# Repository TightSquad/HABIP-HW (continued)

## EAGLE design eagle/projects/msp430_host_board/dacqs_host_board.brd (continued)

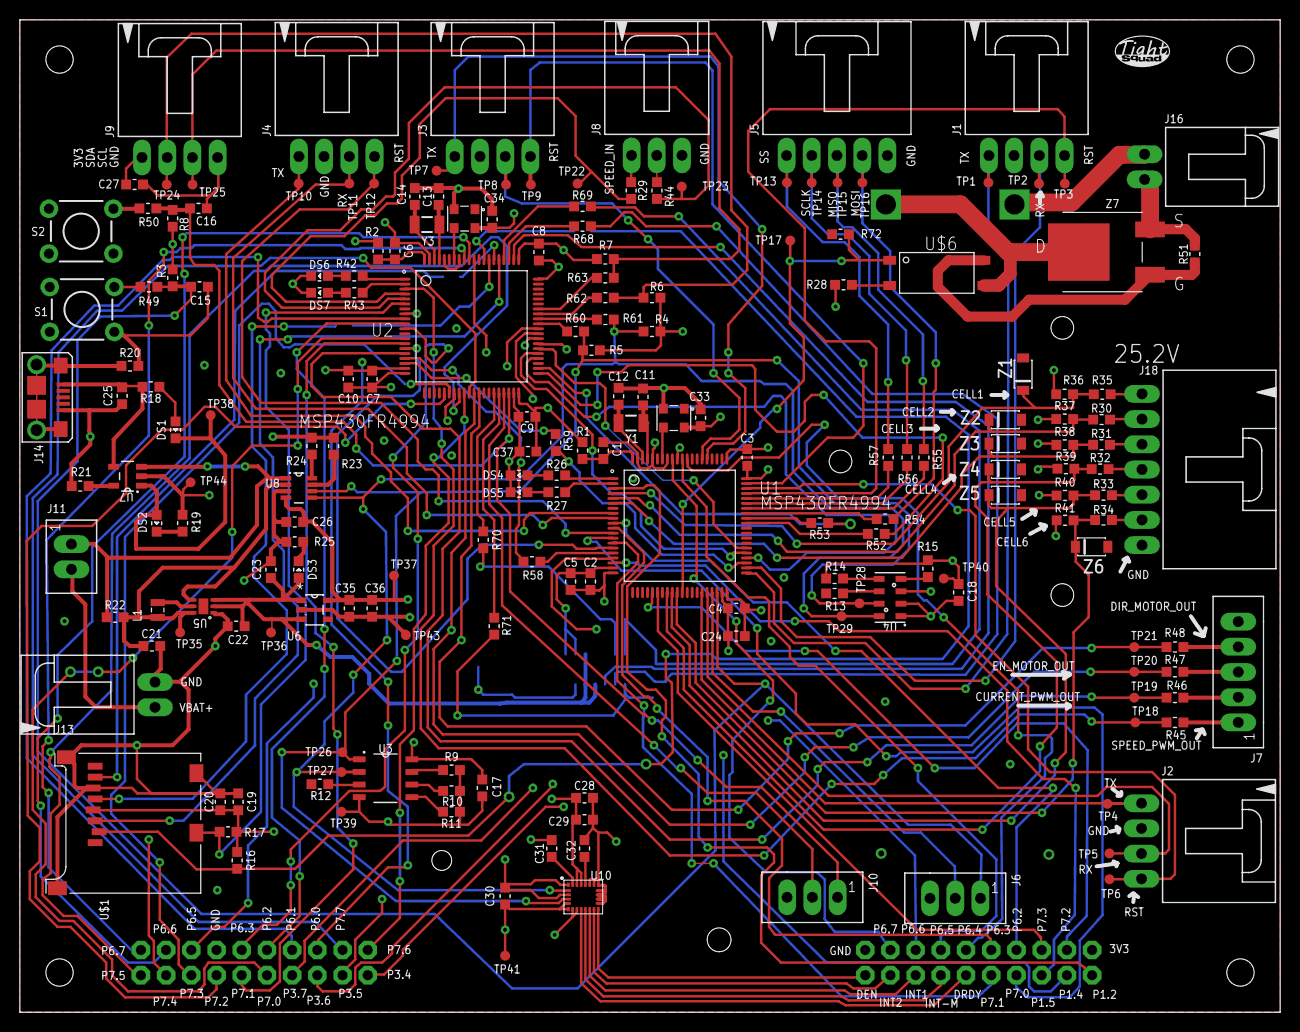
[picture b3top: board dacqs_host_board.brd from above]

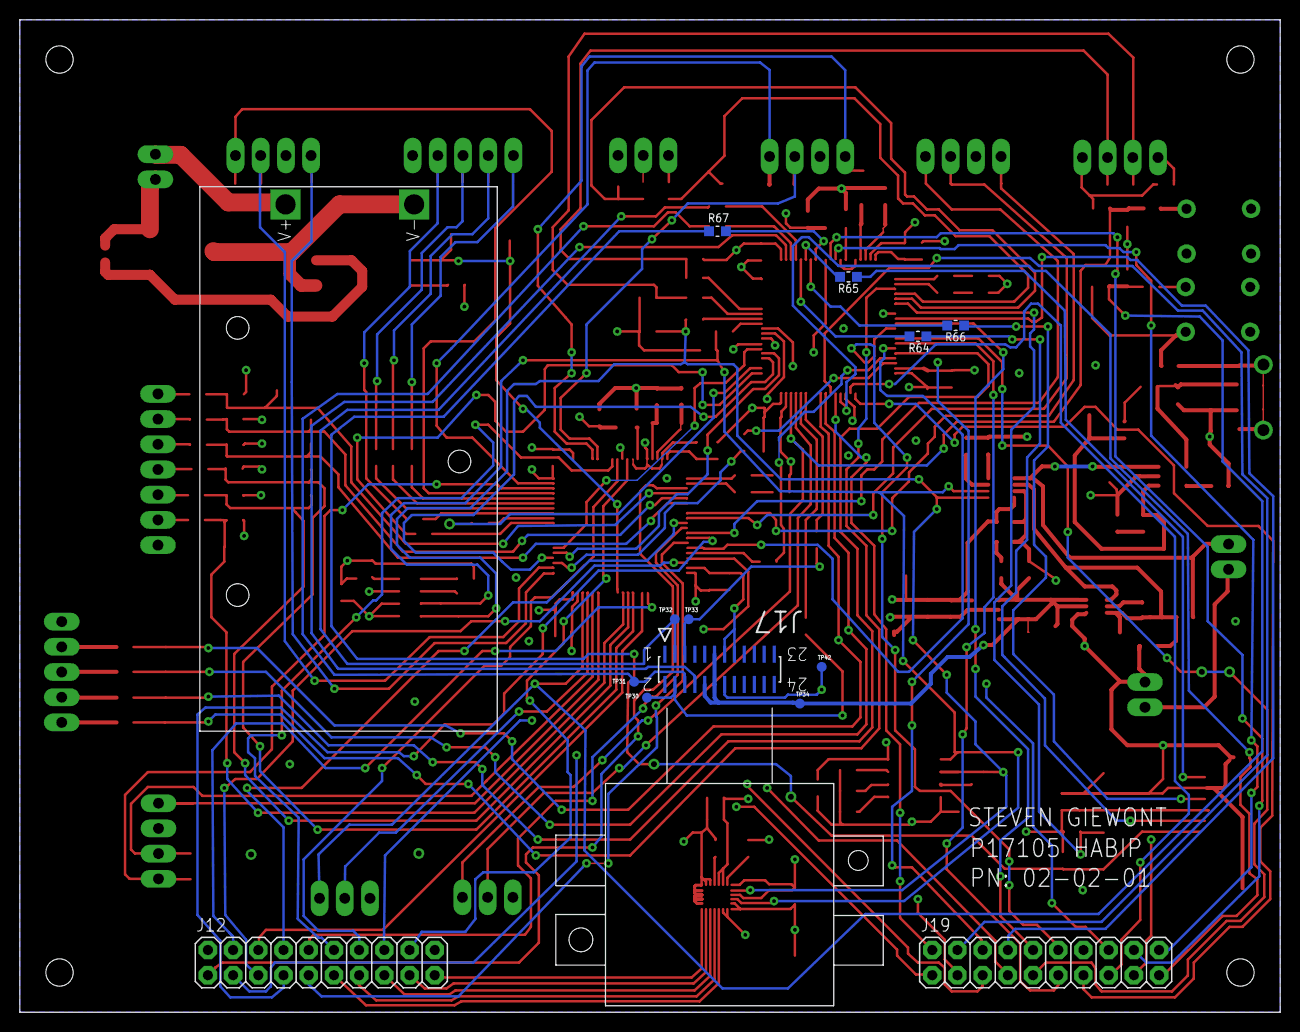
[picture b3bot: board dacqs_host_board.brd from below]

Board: 4 copper layers, 127.0 x 100.0 mm, 272 parts (14 on the bottom side), 172 nets.

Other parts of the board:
U$8: SQUAD_LOGO

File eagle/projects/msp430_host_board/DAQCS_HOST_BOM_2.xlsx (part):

Qty | Value | Device | Package | Parts | Description | FINISH | MANUFACTURER | MANUFACTURER_PN | MOUNT_ANGLE | TOLERANCE | VALUE | VENDOR | VENDOR_PN
18 | 0 | RES_0R0_0603 | R0603 | R1, R2, R9, R10, R11, R12, R13, R14, R15, R20, R23, R24, R29, R44, R45, R46, R4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 | Chip Resistor |  | Panasonic | ERJ-3GEY0R00V |  | JUMPER | 0 | Digi-key | P0.0GCT-ND
1 | 1-Cell 2500mAh Li-Ion Battery | BOM_LINE_ITEM_BLI11 | BLANK | BOM63 |  |  | Adafruit | 328 |  |  | 1-Cell 2500mAh Li-Ion Battery | Adafruit | 328
3 | 10000pF | CAP_10000PF0_0603 | C0603 | C32, C33, C34 | Chip Capacitor |  | AVX Corporation | 06035C103KAT4A |  | ±10% | 10000pF | Digi-key | 478-10055-1-ND
2 | 1000pF | CAP_1000PF0_0603 | C0603 | C15, C16 | Chip Capacitor |  | Murata | GRM188R71H102KA01D |  | 0.1 | 1000pF | Digi-key | 490-1494-1-ND
1 | 100k | RES_100R0_0603 | R0603 | R17 | Chip Resistor |  | Panasonic | ERJ-3EKF1003V |  | 0.01 | 100k | Digi-key | P100KHCT-ND
17 | 100nF | CAP_100NF0_0603 | C0603 | C1, C2, C3, C4, C6, C7, C8, C9, C17, C18, C20, C26, C27, C29, C30, C31, C36 | Chip Capacitor |  | Murata | GRM188R71C104KA01D |  | 0.1 | 100nF | Digi-key | 490-1532-1-ND
1 | 10k | RES_10R0_0603 | R0603 | R37 | Chip Resistor |  | Panasonic | ERJ-3EKF1002V |  | 0.01 | 10k | Digi-key | P10.0KHCT-ND
5 | 10uF | CAP_10UF0_0603 | C0603 | C5, C10, C25, C28, C35 | Chip Capacitor |  | Murata | GRM188R61A106KE69D |  | 0.1 | 10uF | Digi-key | 490-10474-1-ND
1 | 12k | RES_12R0_0603 | R0603 | R34 | Chip Resistor |  | Panasonic | ERJ-3EKF1202V |  | 0.01 | 12k | Digi-key | P12.0KHCT-ND
2 | 15k | RES_15R0_0603 | R0603 | R38, R39 | Chip Resistor |  | Panasonic | ERJ-3EKF1502V |  | 0.01 | 15k | Digi-key | P15.0KHCT-ND
1 | 1k | RES_1R0_0603 | R0603 | R25 | Chip Resistor |  | Panasonic | ERJ-3EKF1001V |  | 0.01 | 1k | Digi-key | P1.00KHCT-ND
4 | 1uF | CAP_1UF0_0603 | C0603 | C19, C23, C24, C37 | Chip Capacitor |  | Murata | GRM033R61A105ME15D |  | 0.2 | 1uF | Digi-key | 490-13226-1-ND
1 | 1uH | IND_1UH0_0805 | WE-PMI_0805 | L1 | Power Multilayer Inductor |  | Murata | LQM21PN1R0MC0D |  | 0.2 | 1uH | Digi-key | 490-4992-1-ND
1 | 2.2uF | CAP_2UF2_0603 | C0603 | C21 | Chip Capacitor |  | Murata | GRM188R61C225KE15D |  | 0.1 | 2.2uF | Digi-key | 490-3296-1-ND
4 | 2.61k | RES_2R61_0603 | R0603 | R4, R5, R6, R7 | Chip Resistor |  | Panasonic | ERJ-3EKF2611V |  | 0.01 | 2.61k | Digi-key | P2.61KHCT-ND
4 | 22pF | CAP_22PF0_0603 | C0603 | C11, C12, C13, C14 | Chip Capacitor |  | Murata | GQM1885C1H220JB01D |  | 0.05 | 22pF | Digi-Key | 490-3575-1-ND
20 | 23.2 | RES_0R23S2_0603 | R0603 | R52, R53, R54, R55, R56, R57, R58, R59, R60, R61, R62, R63, R64, R65, R66, R67,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 | Chip Resistor |  | Panasonic | ERJ-3EKF23R2V |  | 0.01 | 23.2 | Digi-key | P23.2HCT-ND
7 | 2k | RES_2R0_0603 | R0603 | R18, R19, R21, R26, R27, R42, R43 | Chip Resistor |  | Panasonic | ERJ-3EKF2001V |  | 0.01 | 2k | Digi-key | P2.00KHCT-ND
2 | 30k | RES_30R0_0603 | R0603 | R40, R41 | Chip Resistor |  | Panasonic | ERJ-3EKF3002V |  | 0.01 | 30k | Digi-key | P30.0KHCT-ND
2 | 32.768kHz | CRYSTAL3.2X1.5MM | CRYSTAL-SMD-3.2X1.5MM | Y1, Y3 | Various standard crystals. Proven footprints. |  | Epson | FC-135R |  | 20ppm |  | Digi-key | SER4071CT-ND
1 | 4 | RES_4R0_0603 | R0603 | R22 | Chip Resistor |  | Yageo | RL0603FR-070R4L |  | 0.01 | 4 | Digi-key | 311-.4QCT-ND
1 | 4.7uF | CAP_4UF7_0603 | C0603 | C22 | Chip Capacitor |  | Murata | GRM188R61A475KE15D |  | 0.1 | 4.7uF | Digi-key | 490-10477-1-ND
6 | 47k | RES_47R0_0603 | R0603 | R3, R8, R16, R49, R50, R51 | Chip Resistor |  | Panasonic | ERJ-3EKF4702V |  | 0.01 | 47k | Digi-key | P47.0KHCT-ND
4 | 49.9k | RES_49R9_0603 | R0603 | R28, R32, R33, R35 | Chip Resistor |  | Panasonic | ERJ-3EKF4992V |  | 0.01 | 49.9k | Digi-key | P49.9KHCT-ND
1 | 60.4k | RES_60R4_0603 | R0603 | R30 | Chip Resistor |  | Panasonic | ERJ-3EKF6042V |  | 0.01 | 60.4k | Digi-key | P60.4KHCT-ND
1 | 69.8k | RES_68R8_0603 | R0603 | R31 | Chip Resistor |  | Panasonic | ERJ-3EKF6982V |  | 0.01 | 69.8k | Digi-key | P69.8KHCT-ND
1 | 7.15k | RES_7R15_0603 | R0603 | R36 | Chip Resistor |  | Panasonic | ERJ-3EKF7151V |  | 0.01 | 7.15k | Digi-key | P7.15KHCT-ND
1 | 9V | BC9VPC | BC9VPC | BAT1 | 9V board-mount battery cradle |  | MPD | BH9VPC |  |  |  | Digi-key | BH9V-PC-ND
2 | ASEMB-24MHZ-XY-T | ASEMB-24MHZ-XY-T | ASEMB-24MHZ-XY-T-PAC | U$4, U$5 |  |  | Abracon LLC | ASEMB-24.000MHZ-XY-T |  |  |  | Digi-key | 535-11123-1-ND
3 | BLUE | LED_B3V2WURTH_0603 | LED0603 | DS3, DS5, DS7 | Chip LED |  | Wurth | 150060BS75000 |  |  | BLUE | Digi-key | 732-4966-1-ND
1 | CLM-112-02-L-D-IMU-MOUNT_IMU | CLM-112-02-L-D-IMU-MOUNT_IMU | SAMTEC_CLM-112-02-L-D-IMU-MOUNT | J17 | MICRO SOCKET, 1.0MM, SMD, 2X12WAY |  | SAMTEC | CLM-112-02-L-D |  |  |  | Digi-key | SAM1129-12-ND
2 | CONN HEADER 20POS .100 DBL" | M10X2 | 2X10 | J12, J19 |  |  | Samtec Inc. | TSW-110-07-F-D |  |  | CONN HEADER 20POS .100 DBL" | Digi-key | SAM9002-ND
3 | GREEN | LED_G3V2WURTH_0603 | LED0603 | DS2, DS4, DS6 | Chip LED |  | Wurth | 150060GS75000 |  |  | GREEN | Digi-key | 732-4971-1-ND
1 | INA219AIDCNR | INA219AIDCNR | SOT65P110X045-8N | U8 | 26-V, Bidirectional, Zero-Drift, High-Side, I2C Out Current/Power Monitor |  | Texas Instruments | INA219AIDCNR |  |  | INA219AIDCNR | Digi-key | 296-23770-1-ND
1 | LP5907_DBV_5 | LP5907_DBV_5 | DBV5 | U6 |  |  | Texas Instruments | lp5907_dbv_5 |  |  |  | Digi-key | 296-38557-1-ND
1 | LSM9DS1 | LSM9DS1 | LGA24-8X4 | U10 | LSM9DS1 3D accelerometer, gyroscope & magnetometer |  | STMicroelectronics | LSM9DS1TR |  |  |  | Digi-key | 497-14946-1-ND
1 | MCP73831T | MCP73831T-2ATI/OT | SOT23P110X060-5N | U7 | IC, BATT CHARGER, Li-Ion Li-Polymer, 500 mA |  | Microchip | MCP73831T-2ATI/OT |  |  | MCP73831T | Digi-key | MCP73831T-2ATI/OTCT-ND
1 | MICROSD | MICROSD | MICROSD | U$1 | Micro-SD / Transflash card holder with SPI pinout |  | 3M | 2908-05WB-MG |  |  |  | Digi-key | 3M5607CT-ND
6 | MM3Z3V3B | MM3Z3V3B | MM3Z3V3B | Z1, Z2, Z3, Z4, Z5, Z6 |  |  | Farichild/ON Semiconductor | MM3Z3V3B |  |  | MM3Z3V3B | Digi-key | MM3Z3V3BCT-ND
2 | MOL-SL-2-RA | MOLSL_2PIN_SL2RA_RA | MOLSL-2-RA | J13, J16 | Molex SL Series 2-Position Connector | GOLD | Molex | 705530001 | RIGHT |  | MOL-SL-2-RA | Digi-key | WM4900-ND
1 | MOL-SL-2-V | MOLSL_2PIN_SL2V_V | MOLSL-2-V | J11 | Molex SL Series 2-Position Connector | GOLD | Molex | 705430001 | VERTICAL |  | MOL-SL-2-V | Digi-key | WM4800-ND
1 | MOL-SL-3-RA | MOLSL_3PIN_SL3RA_RA | MOLSL-3-RA | J8 | Molex SL Series 3-Position Connector | GOLD | Molex | 705530002 | RIGHT |  | MOL-SL-3-RA | Digi-key | WM4901-ND
2 | MOL-SL-3-V | MOLSL_3PIN_SL3V_V | MOLSL-3-V | J6, J10 | Molex SL Series 3-Position Connector | GOLD | Molex | 705430002 | VERTICAL |  | MOL-SL-3-V | Digi-key | WM4801-ND
5 | MOL-SL-4-RA | MOLSL_4PIN_SL4RA_RA | MOLSL-4-RA | J1, J2, J3, J4, J9 | Molex SL Series 4-Position Connector | GOLD | Molex | 705530003 | RIGHT |  | MOL-SL-4-RA | Digi-key | WM4902-ND
1 | MOL-SL-5-RA | MOLSL_5PIN_SL4RA_RA | MOLSL-5-RA | J5 | Molex SL Series 5-Position Connector | GOLD | Molex | 705530004 | RIGHT |  | MOL-SL-5-RA | Digi-key | WM4903-ND
1 | MOL-SL-5-V | MOLSL_5PIN_SL4V_V | MOLSL-5-V | J7 | Molex SL Series 5-Position Connector | GOLD | Molex | 705430004 | VERTICAL |  | MOL-SL-5-V | Digi-key | WM4803-ND
1 | MOLSL-7-RA | MOLSL_7PIN_RA | MOLSL-7-RA | J18 | Molex SL Series 6-Position Connector | Gold | Molex | 70553-0111 | Right |  | MOLSL-7-RA | Digi-key | WM4158-ND
1 | MS560702BA03-50 | MS5607-02BA03_8SMD | SMD125P110X060-8N | U4 | Barometric Pressure Sensor, with stainless steel cap |  | TE Connectivity | MS560702BA03-50 |  |  | MS560702BA03-50 | Digi-key | 223-1198-1-ND
2 | MSP430FR4994 | MSP430FR5994IPNR | PN0080A_N | U1, U2 |  |  | Texas Instruments | MSP430FR5994IPNR |  |  | MSP430FR4994
1 | NTD2955T4G | NTD2955T4G | NTD2955T4G | U$7 |  |  | ON Semiconductor | NTD2955T4G |  |  |  | Digi-key | NTD2955T4GOSCT-ND
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
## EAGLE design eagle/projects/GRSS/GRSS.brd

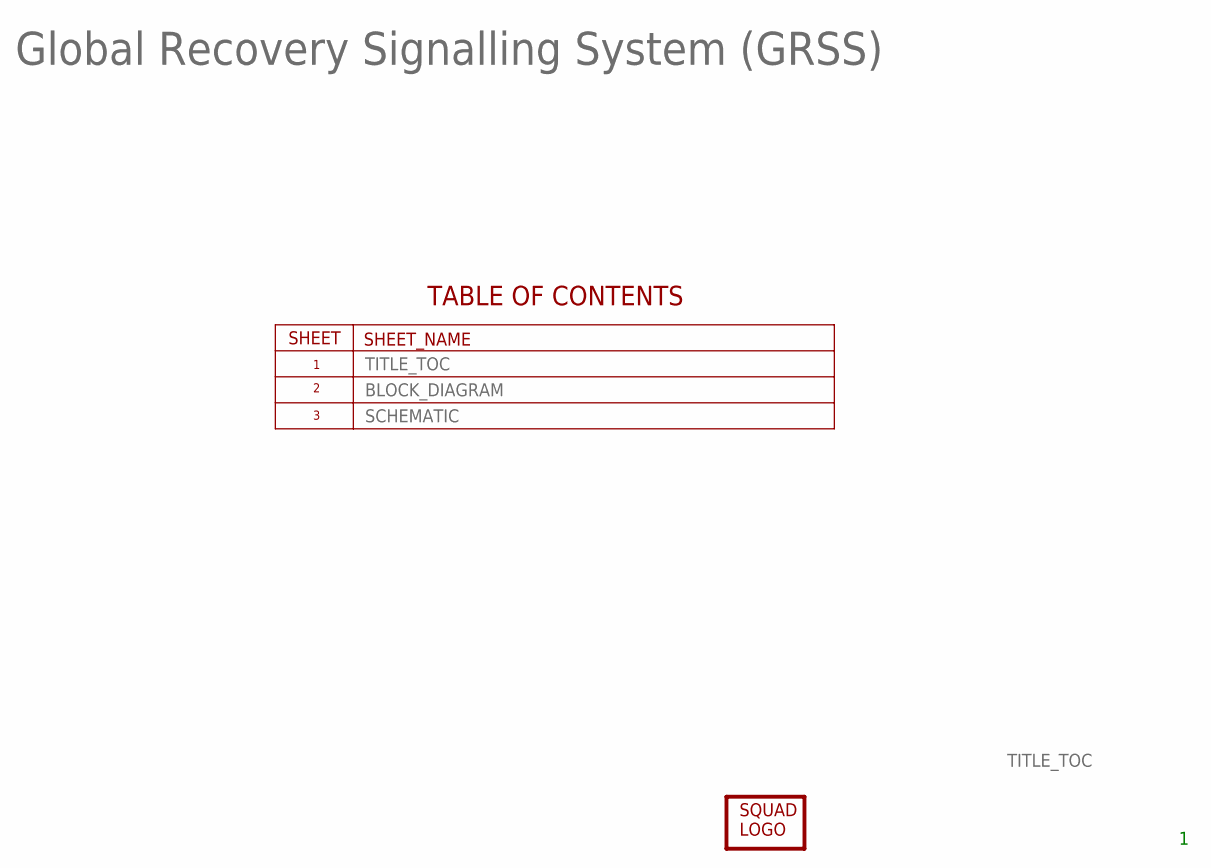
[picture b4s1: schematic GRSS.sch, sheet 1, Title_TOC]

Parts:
LOGO1: LOGO; SQUAD_LOGO

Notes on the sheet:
TITLE_TOC
BLOCK_DIAGRAM
SCHEMATIC
Global Recovery Signalling System (GRSS)

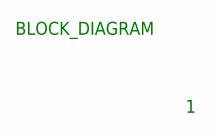
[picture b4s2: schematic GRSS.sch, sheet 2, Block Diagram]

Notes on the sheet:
BLOCK_DIAGRAM

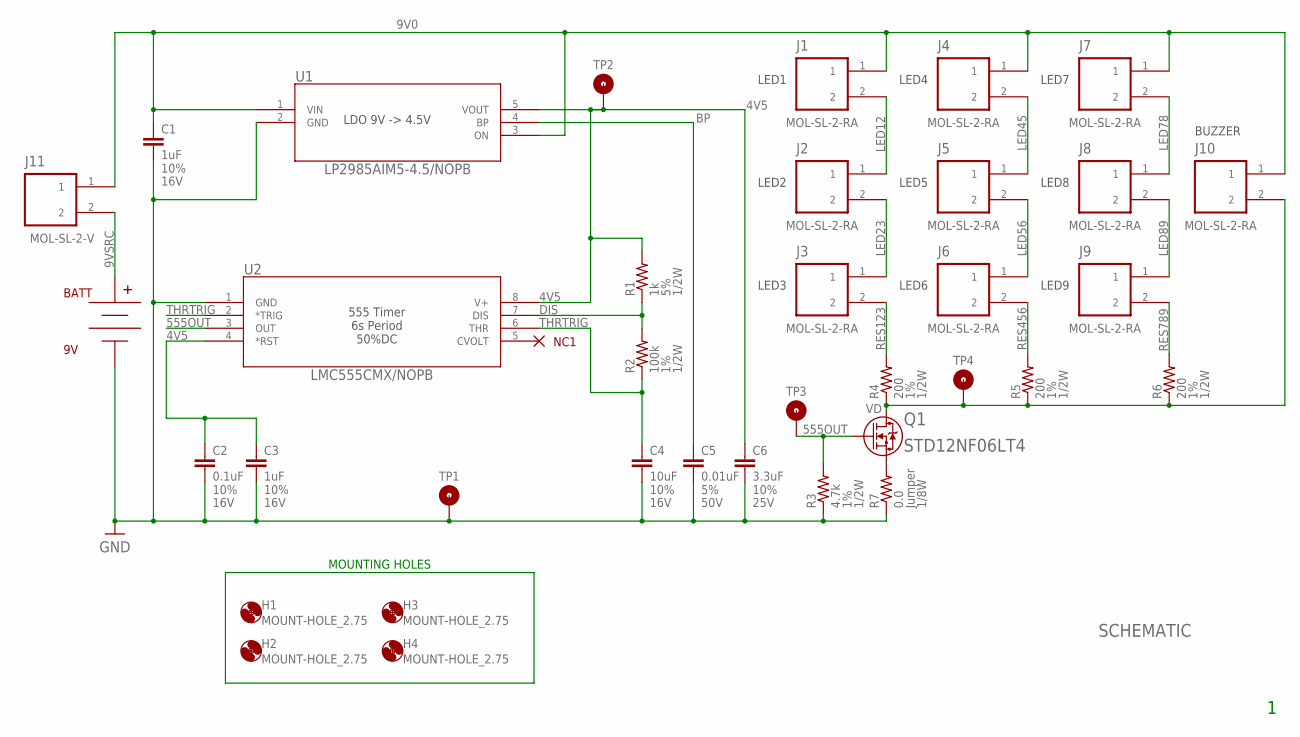
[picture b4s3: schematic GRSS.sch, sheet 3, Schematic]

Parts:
BATT: 9V; BC9VPC
C1, C3: 1uF; C0805
C2: 0.1uF; C0805
C4: 10uF; C0805
C5: 0.01uF; C0805
C6: 3.3uF; C0805
H1, H2, H3, H4: MOUNT-HOLE_2.75; 2,75_HOLE_RASPI
J1, J2, J3, J4, J5, J6, J7, J8, J9, J10: MOL-SL-2-RA; MOLSL-2-RA
J11: MOL-SL-2-V; MOLSL-2-V
Q1: STD12NF06LT4; DPAK
R1: 1k; R0805
R2: 100k; R0805
R3: 4.7k; R0805
R4, R5, R6: 200; R0805
R7: 0.0; R0805
TP1: GND; TP10R
TP2: 4V5; TP10R
TP3: 555OUT; TP10R
TP4: VD; TP10R
U1: LP2985AIM5-4.5/NOPB; MF05A
U2: LMC555CMX/NOPB; M08A

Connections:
4V5: C2.1, C3.1, C6.1, R1.2, TP2.TP, U1.5 (VOUT), U2.4 (*RST), U2.8 (V+)
9V0: C1.1, J1.1, J4.1, J7.1, J10.1, J11.1, U1.1 (VIN), U1.3 (ON)
9VSRC: BATT.V+, J11.2
555OUT: Q1.1, R3.2, TP3.TP, U2.3 (OUT)
BP: C5.1, U1.4 (BP)
DIS: R1.1, R2.2, U2.7 (DIS)
GND: BATT.V-, C1.2, C2.2, C3.2, C4.2, C5.2, C6.2, R3.1, R7.1, TP1.TP, U1.2 (GND), U2.1 (GND)
LED12: J1.2, J2.1
LED23: J2.2, J3.1
LED45: J4.2, J5.1
LED56: J5.2, J6.1
LED78: J7.2, J8.1
LED89: J8.2, J9.1
NC: U2.5 (CVOLT)
RES123: J3.2, R4.2
RES456: J6.2, R5.2
RES789: J9.2, R6.2
THRTRIG: C4.1, R2.1, U2.2 (*TRIG), U2.6 (THR)
VD: J10.2, Q1.3 (2), R4.1, R5.1, R6.1, TP4.TP
ZEROOHM: Q1.2 (3), R7.2

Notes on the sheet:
LED1
LED2
LED3
LED4
LED5
LED6
LED7
LED8
LED9
BUZZER
555 Timer 6s Period 50%DC
LDO 9V -> 4.5V
SCHEMATIC
MOUNTING HOLES

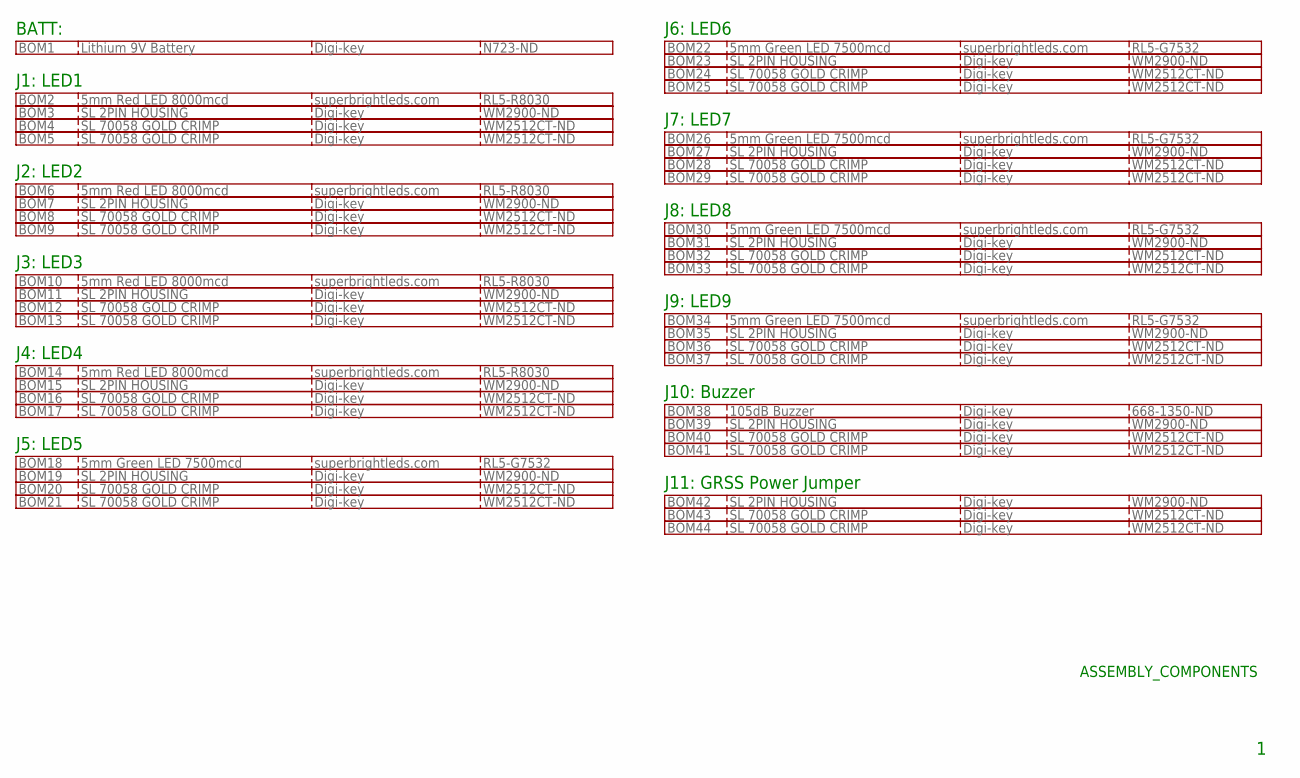
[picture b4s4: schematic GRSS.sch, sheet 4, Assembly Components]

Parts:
BOM1: Lithium 9V Battery; BLANK
BOM2, BOM6, BOM10, BOM14: 5mm Red LED 8000mcd; BLANK
BOM3, BOM7, BOM11, BOM15, BOM19, BOM23, BOM27, BOM31, BOM35, BOM39, BOM42: SL 2PIN HOUSING; BLANK
BOM4, BOM5, BOM8, BOM9, BOM12, BOM13, BOM16, BOM17, BOM20, BOM21, BOM24, BOM25, BOM28, BOM29, BOM32, BOM33, BOM36, BOM37, BOM40, BOM41, BOM43, BOM44: SL 70058 GOLD CRIMP; BLANK
BOM18, BOM22, BOM26, BOM30, BOM34: 5mm Green LED 7500mcd; BLANK
BOM38: 105dB Buzzer; BLANK

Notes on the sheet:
BATT:
J1: LED1
J2: LED2
J3: LED3
J4: LED4
J5: LED5
J6: LED6
J7: LED7
J8: LED8
J9: LED9
J10: Buzzer
J11: GRSS Power Jumper
ASSEMBLY_COMPONENTS

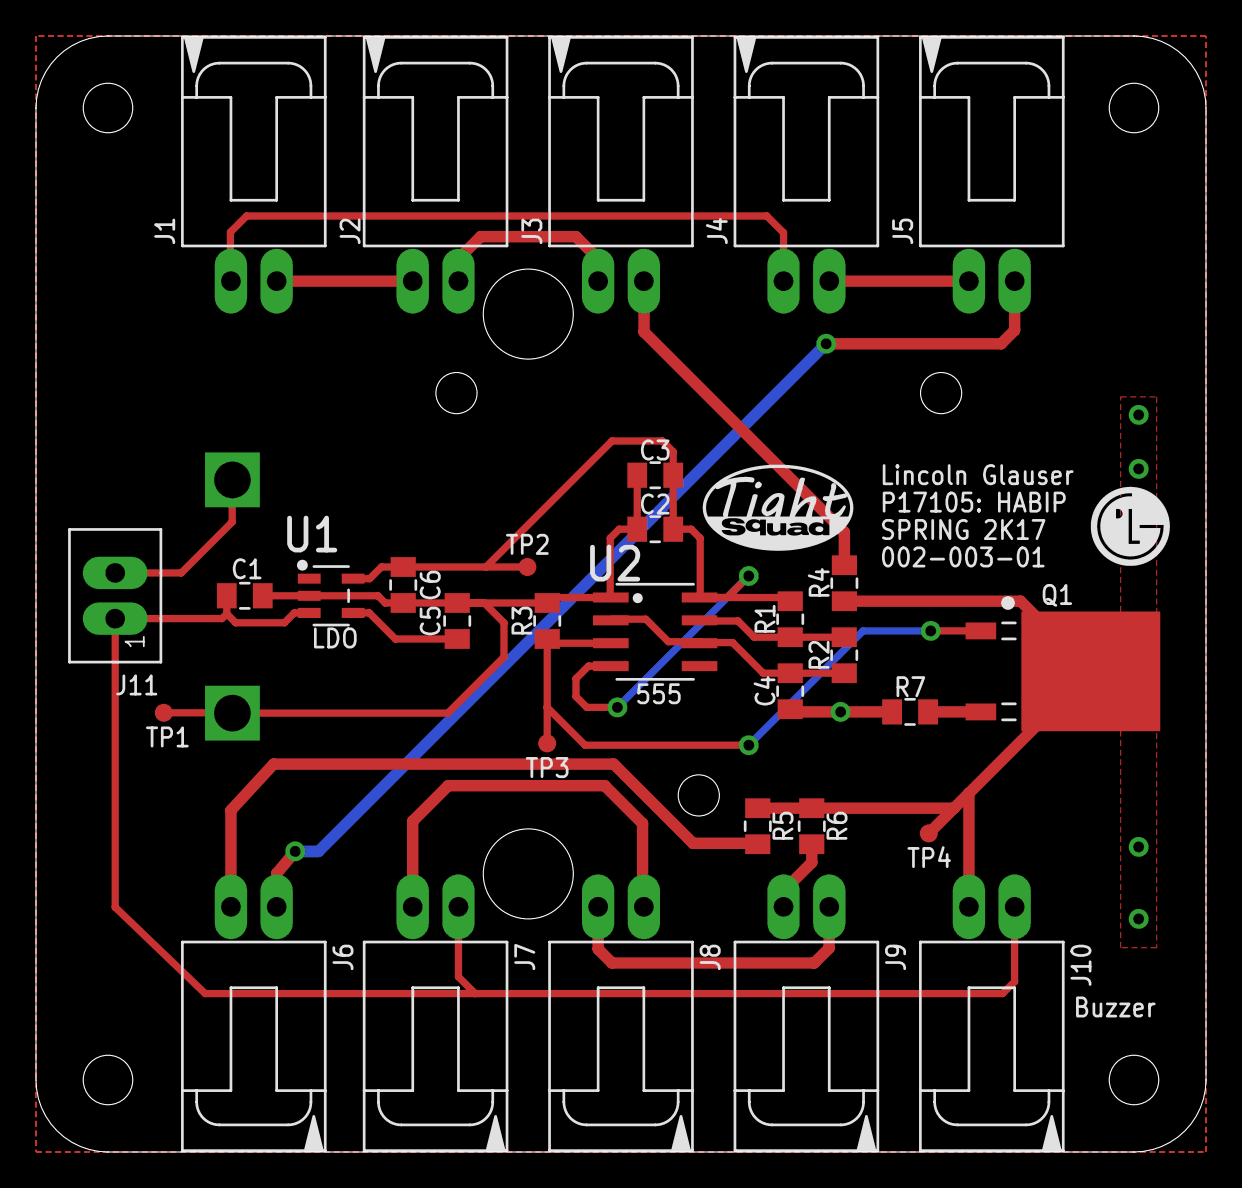
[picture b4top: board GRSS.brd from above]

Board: 4 copper layers, 65.0 x 62.0 mm, 82 parts (1 on the bottom side), 19 nets.

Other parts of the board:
E$1: LG

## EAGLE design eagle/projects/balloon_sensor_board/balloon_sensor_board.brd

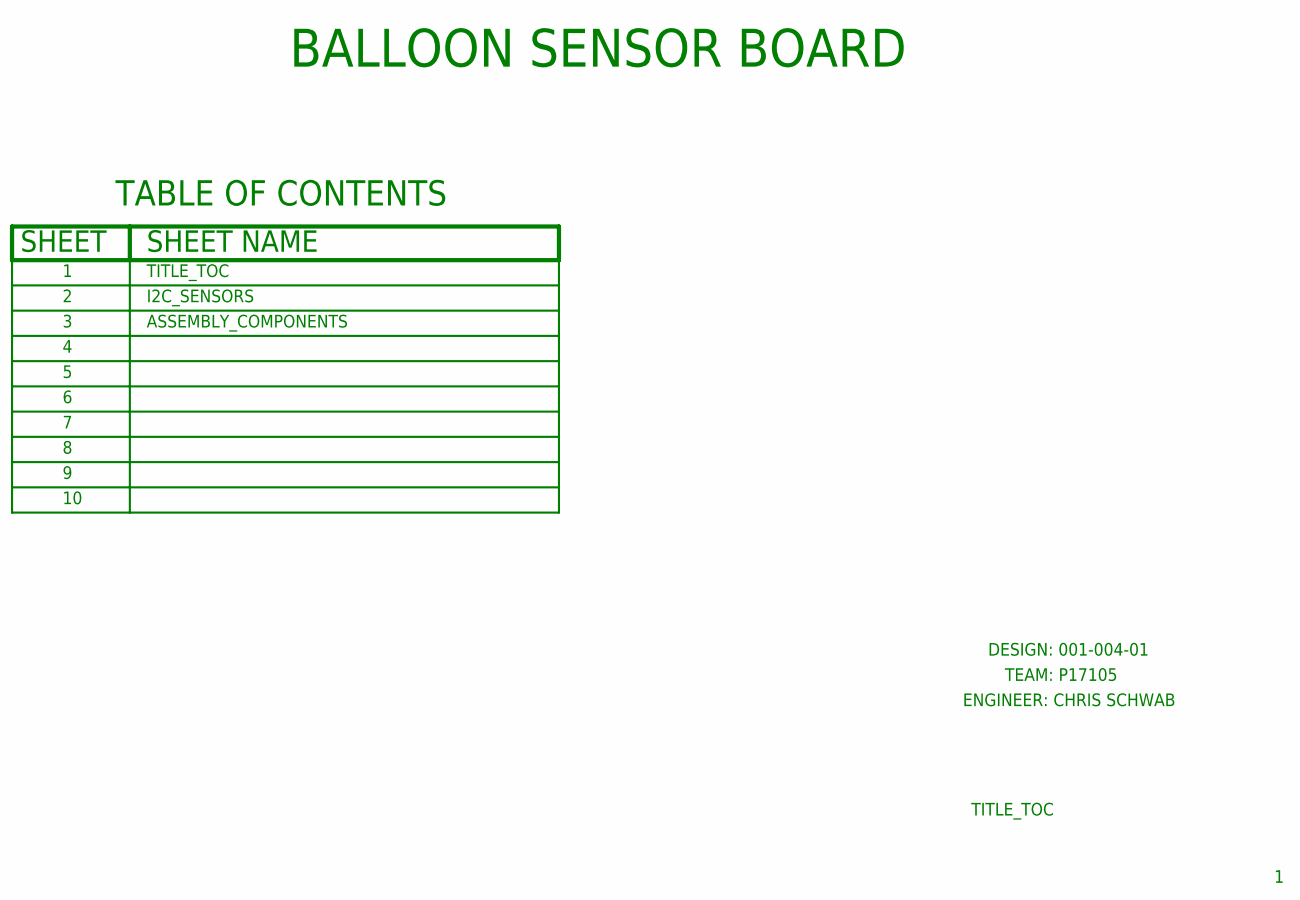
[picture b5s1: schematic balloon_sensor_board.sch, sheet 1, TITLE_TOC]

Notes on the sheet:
BALLOON SENSOR BOARD
TITLE_TOC
I2C_SENSORS
ENGINEER: CHRIS SCHWAB
TEAM: P17105
DESIGN: 001-004-01
ASSEMBLY_COMPONENTS

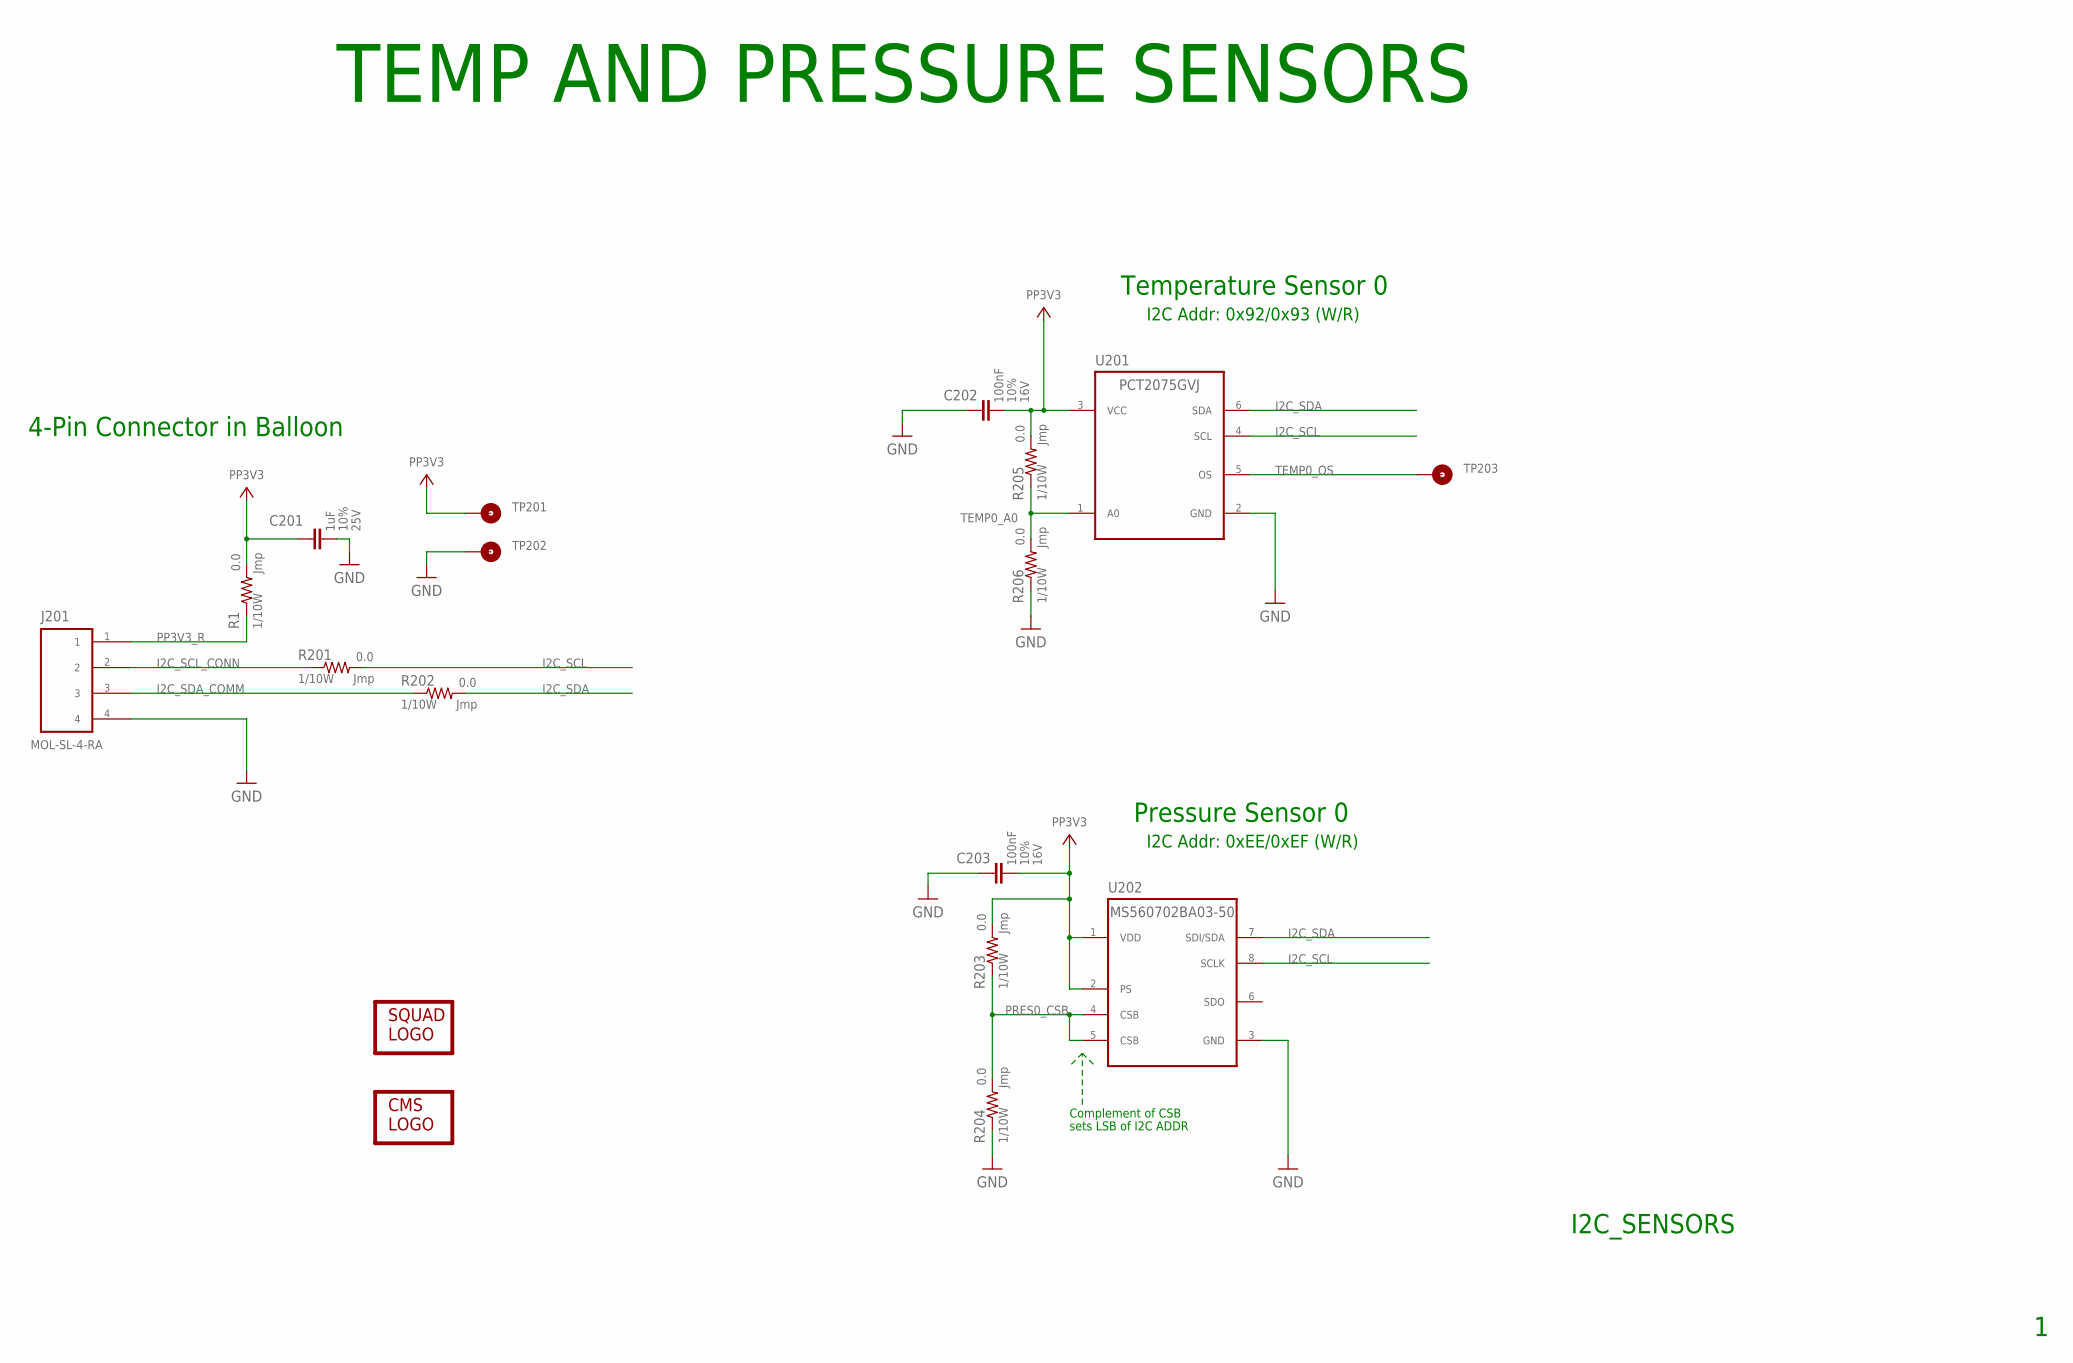
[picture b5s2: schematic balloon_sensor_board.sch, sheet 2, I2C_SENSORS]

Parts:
C201: 1uF; C0603
C202, C203: 100nF; C0603
J201: MOL-SL-4-RA; MOLSL-4-RA
LOGO201: SQUAD_LOGO
LOGO202: CMS_LOGO
R1, R201, R202, R203, R204, R205, R206: 0.0; R0603
TP201, TP202, TP203: TEST_POINT_SMT_15R_SMD; TP15R
U201: PCT2075GVJ; TSOP95P080X055-6N
U202: MS560702BA03-50; SMD125P110X060-8N

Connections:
GND: C201.2, C202.1, C203.1, J201.4, R204.1, R206.1, TP202.TP, U201.2 (GND), U202.3 (GND)
I2C_SCL: R201.2, U201.4 (SCL), U202.8 (SCLK)
I2C_SCL_CONN: J201.2, R201.1
I2C_SDA: R202.2, U201.6 (SDA), U202.7 (SDI/SDA)
I2C_SDA_COMM: J201.3, R202.1
PP3V3: C201.1, C202.2, C203.2, R1.2, R203.2, R205.2, TP201.TP, U201.3 (VCC), U202.1 (VDD), U202.2 (PS)
PP3V3_R: J201.1, R1.1
PRES0_CSB: R203.1, R204.2, U202.4 (CSB), U202.5 (CSB)
TEMP0_A0: R205.1, R206.2, U201.1 (A0)
TEMP0_OS: TP203.TP, U201.5 (OS)

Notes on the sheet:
TEMP AND PRESSURE SENSORS
I2C_SENSORS
Pressure Sensor 0
Complement of CSB
sets LSB of I2C ADDR
I2C Addr: 0xEE/0xEF (W/R)
Temperature Sensor 0
I2C Addr: 0x92/0x93 (W/R)
4-Pin Connector in Balloon

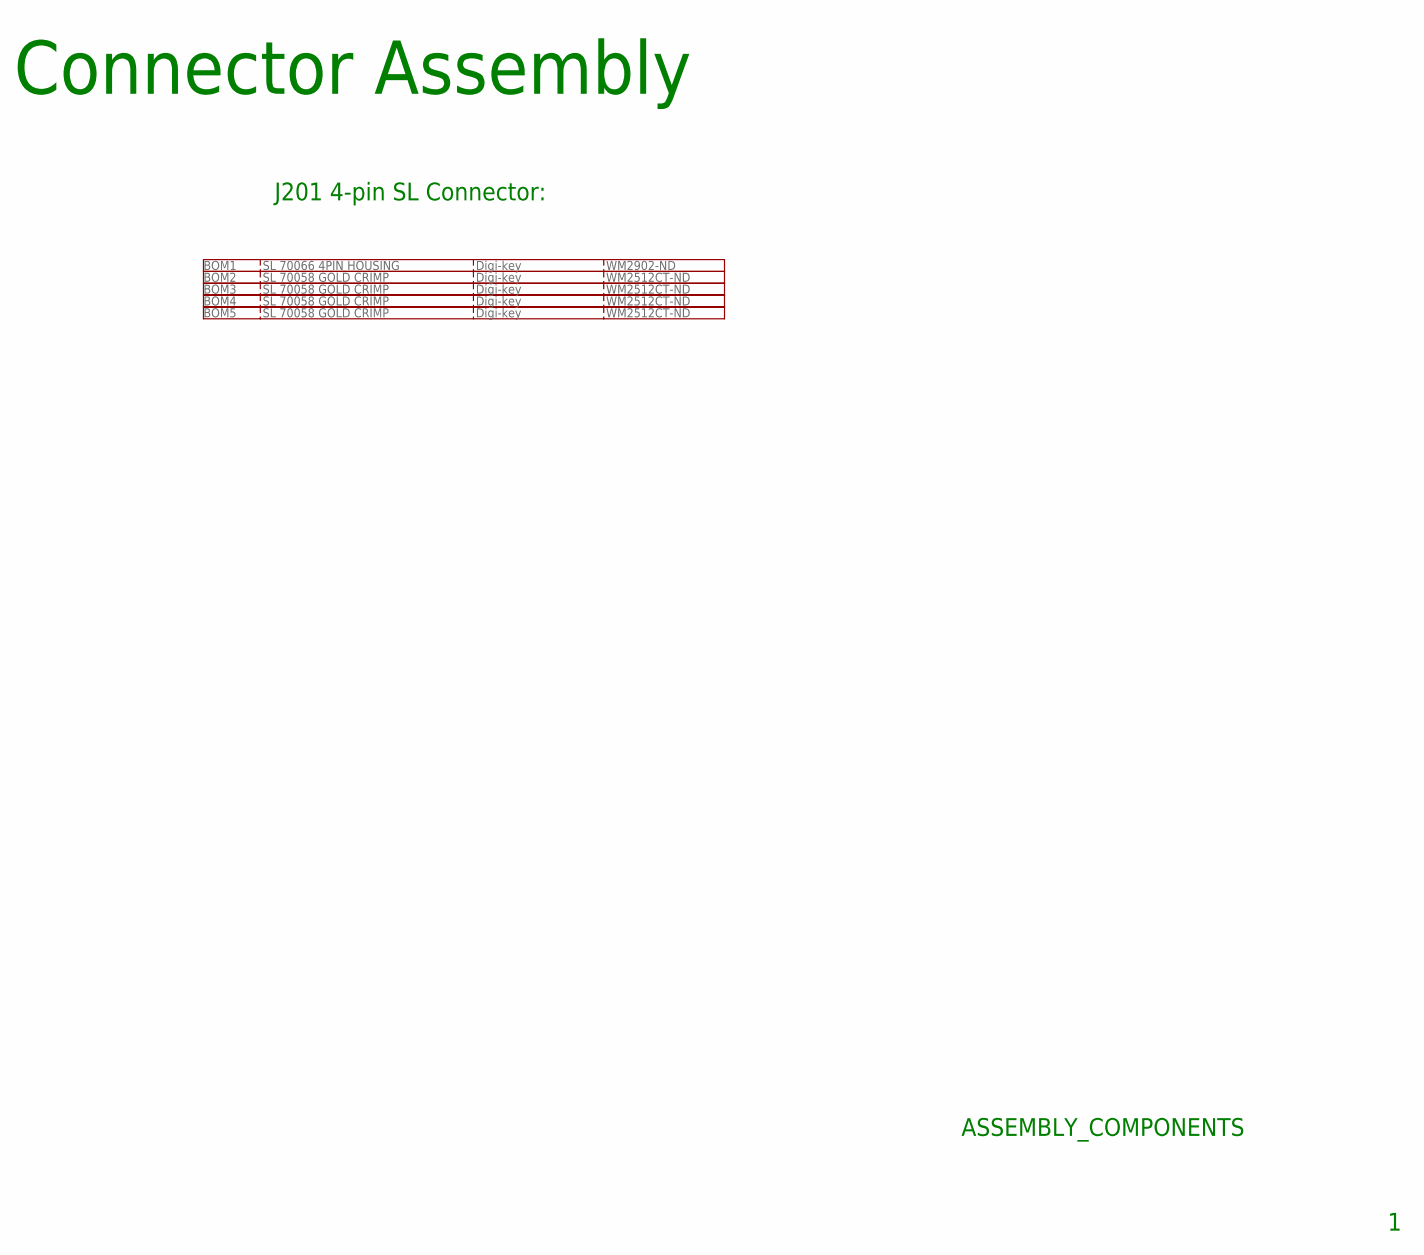
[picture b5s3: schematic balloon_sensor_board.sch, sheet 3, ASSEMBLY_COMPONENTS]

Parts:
BOM1: SL 70066 4PIN HOUSING; BLANK
BOM2, BOM3, BOM4, BOM5: SL 70058 GOLD CRIMP; BLANK

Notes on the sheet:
ASSEMBLY_COMPONENTS
Connector Assembly
J201 4-pin SL Connector:

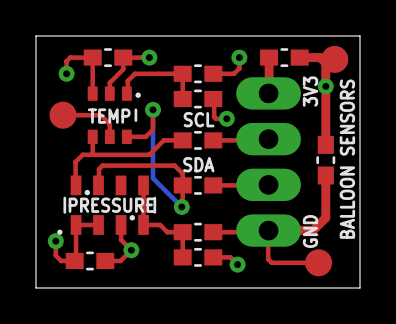
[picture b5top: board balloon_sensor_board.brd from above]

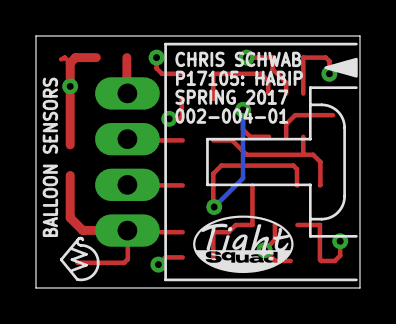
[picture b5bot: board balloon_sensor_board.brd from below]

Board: 4 copper layers, 18.0 x 14.0 mm, 23 parts (3 on the bottom side), 10 nets.
